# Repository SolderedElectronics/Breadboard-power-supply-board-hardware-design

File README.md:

# Breadboard power supply board Hardware Design

## About the Product

|  |
| :----------------------------------------------------------: |
| [Buy Breadboard power supply board](https://www.solde.red/333084) |

If you need a simple and stable power source for your breadboard projects, this board is here to help. Supply it with DC jack DC power or using UCB-C cable, and the board provides 3.3V, 5V or 12V directly to the power supply lines on the breadboard. Output voltages are adjustable seperately using the onboard switches. There’s a power LED, a power switch and an automatic voltage selection circuit, in case both power inputs are there.

---

## Repository Contents

This repository contains all design files for Breadboard power supply board, organized as follows:

- **`CAD` folder**: Contains KiCAD design files, including:
  - Schematics
  - PCB layout
  - Panel PCB layout
  - Source 3D files in Fusion360, if any
  - All files are sorted by version with a detailed change log.
- **`OUTPUTS` folder**: Includes all production-ready files, such as:
  - Bill of Materials (BOM) and interactive BOM (iBOM)
  - PDF versions of schematics
  - 3D `.step` file of the board
  - 3D-printable models
  - Gerber files for PCB manufacturing
  - Image of the pinout of the board
  - Product image
  - Compliance, legal and generic sales documents

Refer to the `Change Log` in the CAD folder for details about updates between versions.

---

## Learn More About the Product

Beyond the repository, explore the following resources:

### Soldered Verify

The **Soldered Verify** system ensures every board you purchase from Soldered is fully functional. It also provides access to exclusive test data for your product. To get started, find the unique Soldered Verify ID on your product's packaging and enter the ID on the [Soldered Verify page](https://soldered.com/verify/) to access test results and additional product details.

### Soldered Community

Soldered Community is your go-to place for technical support. Our engineers track and answer all questions posted there, and it’s a great space for the maker community. Get answers to your questions and solutions for your challenges at [Soldered Community](https://soldered.com/community).

### solde.red

solde.red is an ultimate URL shortener and information hub. Access it by typing solde.red/ followed by your product SKU, e.g., [solde.red/333000](https://solde.red/333000), to find getting-started guides, datasheets, open-source hardware and software files, certifications, images, pinouts, and more. Read more about the shortener [here](https://solde.red/info/).

---

## Contributing

Contributions are welcome! Here’s how you can get involved:

- Submit pull requests to enhance the design or fix issues.
- Report bugs or problems by opening an issue.

We encourage community collaboration to make this product even better.

---

## About Soldered

[Soldered for Makers](https://soldered.com) specializes in designing and manufacturing electronic products tailored for enthusiasts, ranging from hobbyists to professionals. Our portfolio includes electronic boards, sensors, and actuators that are widely utilized in fields such as microelectronics, mechatronics, robotics, programming, and IoT. Every product we offer is designed in-house and built upon open-source hardware and software platforms. Proudly certified and manufactured within the European Union, our catalog likely includes the product you need for your project.

We complement these products with comprehensive tutorials and manuals, product descriptions, schematics, programming codes, and project examples. Our round-the-clock [customer and technical support](https://soldered.com/community) is available for all our products, irrespective of the sales channel. Soldered’s success and services reflect our maker community’s unwavering [trust](https://www.trustpilot.com/review/soldered.com), for which we are deeply grateful. Join our community and create using Soldered products.

---

## License

All Soldered open-source hardware (OSH) is under The TAPR Open Hardware License. Read more in the LICENSE file located in this repository.

**Disclaimer:**

No warranty - all designs in this repository are distributed in the hope that they will be useful, but without any warranty. They are provided "AS IS", therefore without warranty of any kind, either expressed or implied. The entire quality and performance of what you do with the contents of this repository are your responsibility. In no event Soldered Electronics will be liable for your damages, or losses, including any general, special, incidental, or consequential damage arising out of the use or inability to use the contents of this repository. 

---

## Have fun!

Thank you for your support from your fellow makers at Soldered Electronics.

Happy Making!

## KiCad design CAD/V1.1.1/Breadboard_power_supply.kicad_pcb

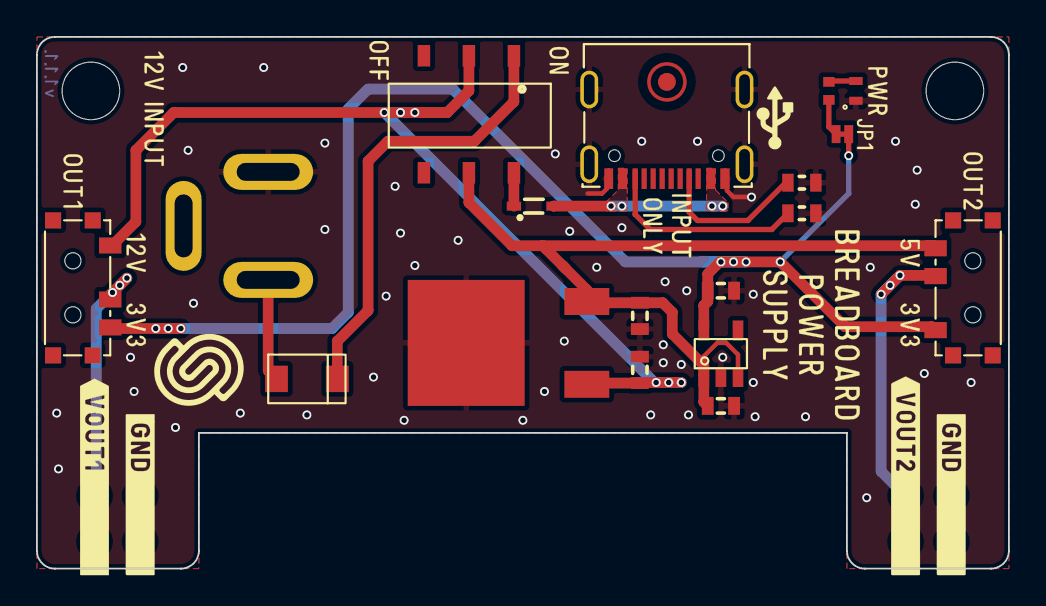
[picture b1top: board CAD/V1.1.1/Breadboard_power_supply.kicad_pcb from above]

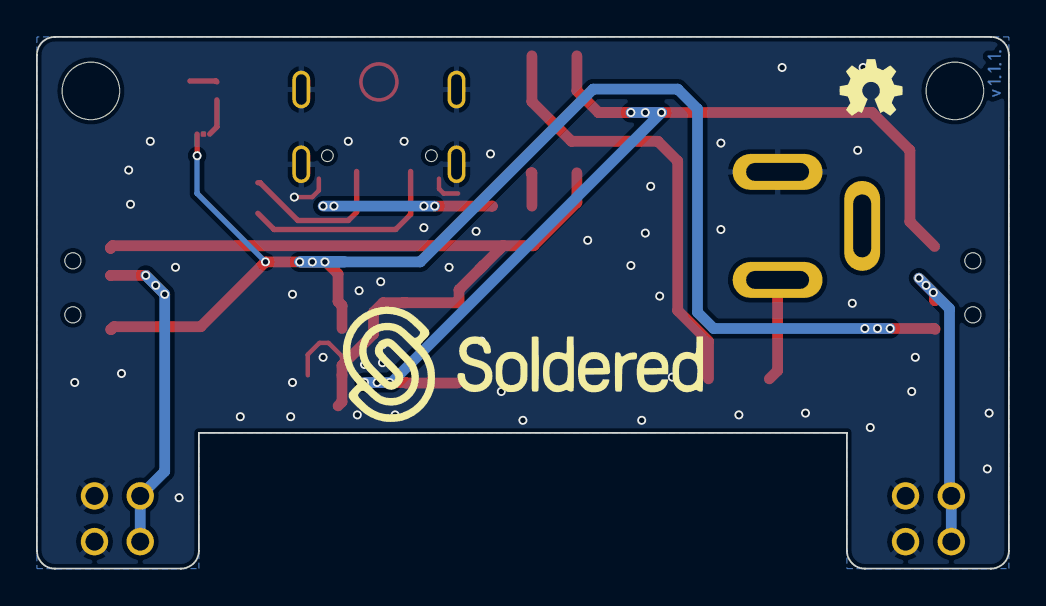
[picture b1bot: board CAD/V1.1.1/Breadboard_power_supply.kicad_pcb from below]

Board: 2 copper layers, 54.0 x 29.5 mm, 25 parts (4 on the bottom side), 14 nets.

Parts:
C1, C4: 2.2uF; 0603C
C2: 1uF; 0603C
C3: 0.1uF; 0603C
D1: BAT20J; SOD-323
D2: M4_DIODA
D3: purple; 0402LED
FD1: FIDUCIAL; FIDUCIAL_23
H1, H2: HOLE_3.2mm
JP1: SMD-JUMPER-CONNECTED_TRACE_SLODERMASK
K1: U262-161N-4BVC11
K2: DC_JACK
K3, K4, K5, K6: HEADER_MALE_2X1
R1, R2: 5.1k; 0603R
R3: 2k2; 0402R
S1: SK-3245S-L3-B
S2, S3: SS-3292S-L1
U1: 7805; AS7805ADTR
U2: SE5218; SOT-23-5

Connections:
3V3: C4.2, JP1.1, S2.3, S3.1, U2.5 (VOUT)
5V: C1.2, C3.2, S1.5, S3.3, U1.2 (OUT), U2.1 (VIN), U2.3 (EN)
12V: C2.2, S1.2, S2.1, U1.1 (IN)
GND: C1.1, C2.1, C3.1, C4.1, D3.2 (K), K1.A1 (GND), K1.A12 (GND), K1.B1 (GND), K1.B12 (GND), K1.SH (SHIELD), K2.2 (VSS), K3.1, K4.1, K5.1, K6.1, R1.2, R2.2, U1.3 (G), U2.2 (GND)
unnamed: D1.1 (A), K1.A4 (VBUS), K1.A9 (VBUS), K1.B4 (VBUS), K1.B9 (VBUS)
unnamed: D2.1 (A), K2.1 (VCC)
unnamed: D3.1 (A), R3.2
unnamed: JP1.2, R3.1
unnamed: K1.A5 (CC1), R2.1
unnamed: K1.B5 (CC2), R1.1
unnamed: K3.2, K5.2, S2.2
unnamed: K4.2, K6.2, S3.2
VIN: D2.2 (K), S1.1
VUSB: D1.2 (K), S1.4

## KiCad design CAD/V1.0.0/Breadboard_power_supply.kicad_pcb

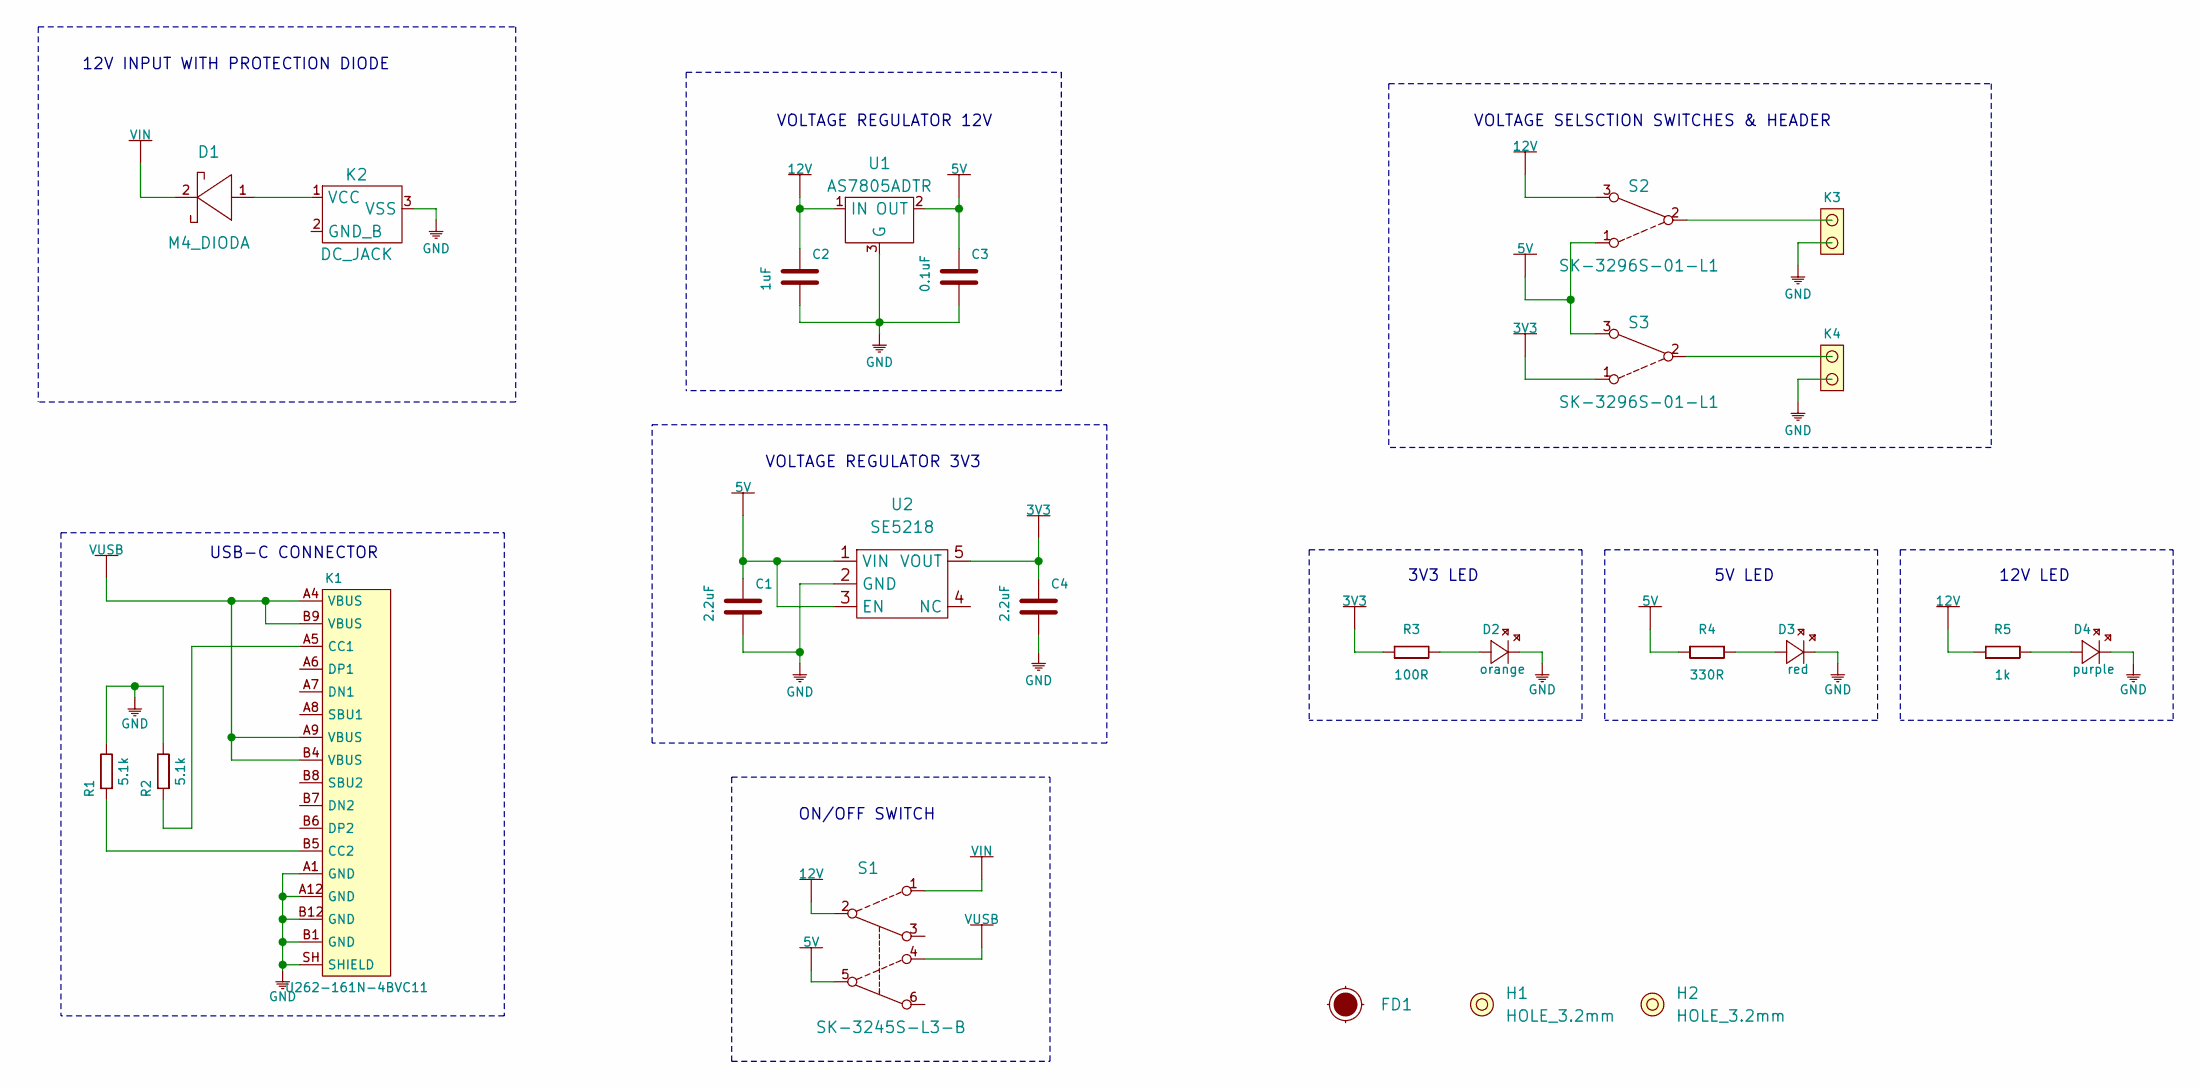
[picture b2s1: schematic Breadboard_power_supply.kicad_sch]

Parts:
C1, C4: 2.2uF; 0603C
C2: 1uF; 0603C
C3: 0.1uF; 0603C
D1: M4_DIODA
D2: orange; 0402LED
D3: red; 0402LED
D4: purple; 0402LED
FD1: Fiducial_Stencil; FIDUCIAL_1MM_PASTE
H1, H2: HOLE_3.2mm
K1: U262-161N-4BVC11
K2: DC_JACK
K3, K4: HEADER_MALE_2X1
R1, R2: 5.1k; 0603R
R3: 100R; 0402R
R4: 330R; 0402R
R5: 1k; 0402R
S1: SK-3245S-L3-B
S2, S3: SK-3296S-01-L1; SWITCH_ON_OFF_ON_3296
U1: AS7805ADTR
U2: SE5218; SOT-23-5

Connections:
3V3: C4.2, R3.1, S3.1, U2.5 (VOUT)
5V: C1.2, C3.2, R4.1, S1.5, S2.1, S3.3, U1.2 (OUT), U2.1 (VIN), U2.3 (EN)
12V: C2.2, R5.1, S1.2, S2.3, U1.1 (IN)
GND: C1.1, C2.1, C3.1, C4.1, D2.2 (K), D3.2 (K), D4.2 (K), K1.A1 (GND), K1.A12 (GND), K1.B1 (GND), K1.B12 (GND), K1.SH (SHIELD), K2.3 (VSS), K3.1, K4.1, R1.2, R2.2, U1.3 (G), U2.2 (GND)
unnamed: D1.1 (A), K2.1 (VCC)
unnamed: D2.1 (A), R3.2
unnamed: D3.1 (A), R4.2
unnamed: D4.1 (A), R5.2
unnamed: K1.A5 (CC1), R2.1
unnamed: K1.B5 (CC2), R1.1
unnamed: K3.2, S2.2
unnamed: K4.2, S3.2
VIN: D1.2 (K), S1.1
VUSB: K1.A4 (VBUS), K1.A9 (VBUS), K1.B4 (VBUS), K1.B9 (VBUS), S1.4

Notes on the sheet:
USB-C CONNECTOR
12V INPUT WITH PROTECTION DIODE
ON/OFF SWITCH
VOLTAGE REGULATOR 3V3
VOLTAGE REGULATOR 12V
3V3 LED
5V LED
VOLTAGE SELSCTION SWITCHES & HEADER
12V LED

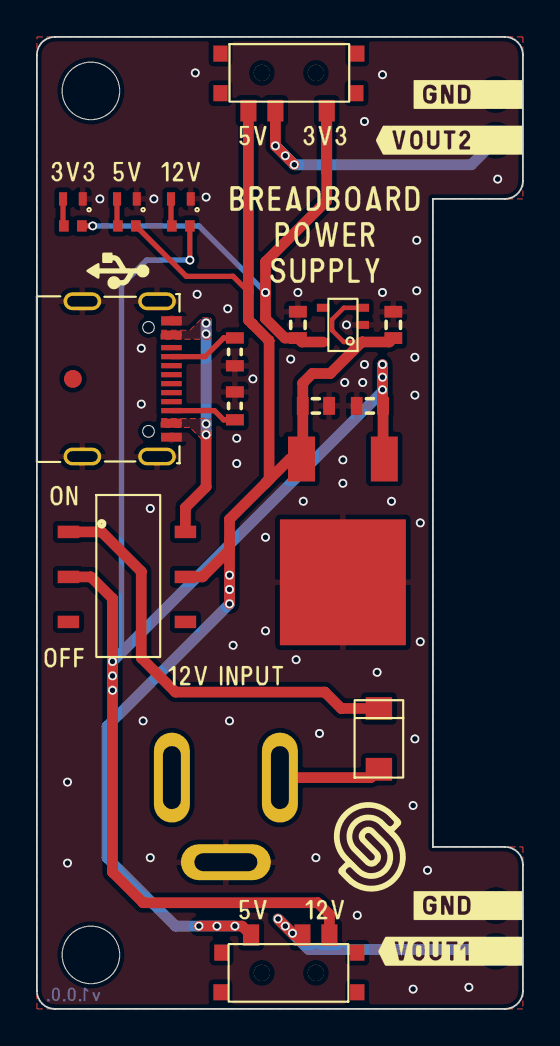
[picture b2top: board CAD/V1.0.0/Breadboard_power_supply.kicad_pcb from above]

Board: 2 copper layers, 27.0 x 54.0 mm, 25 parts (0 on the bottom side), 14 nets.

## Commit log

2022-08-06 Updating open source files.
